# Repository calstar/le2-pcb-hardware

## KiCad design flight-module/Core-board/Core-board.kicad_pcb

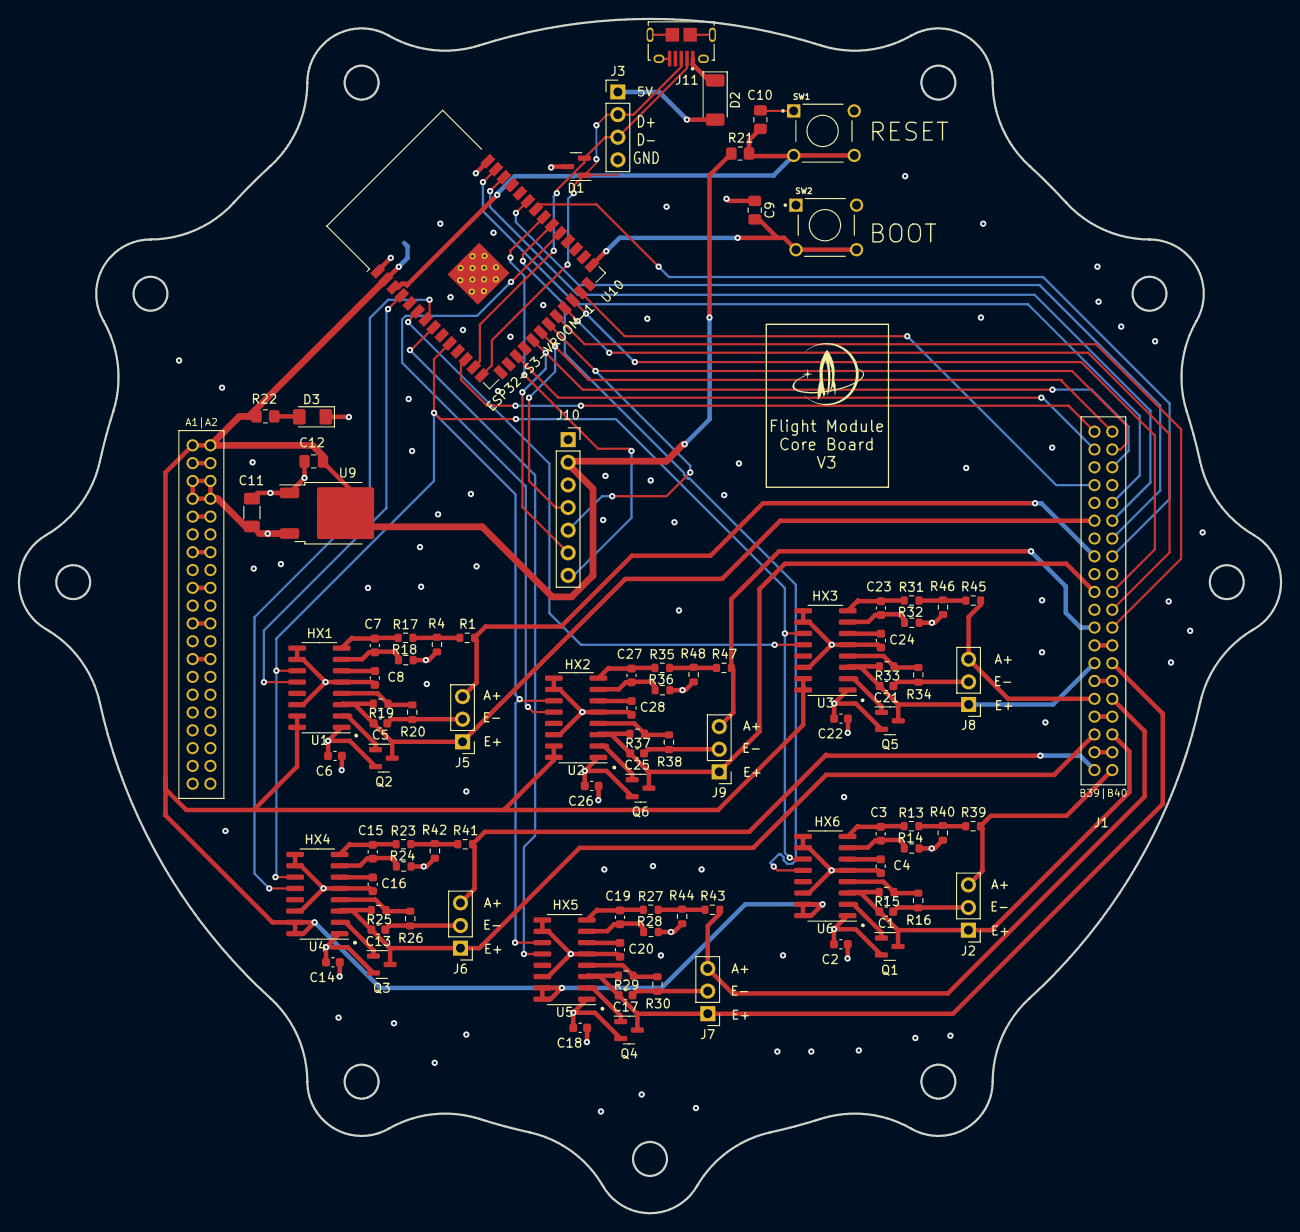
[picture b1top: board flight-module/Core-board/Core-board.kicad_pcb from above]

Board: 4 copper layers, 141.7 x 134.1 mm, 95 parts (0 on the bottom side), 78 nets.

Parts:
C1, C2, C5, C6, C13, C14, C17, C18, C21, C22, C25, C26: 10uF; C_0603_1608Metric
C3, C4, C7, C8, C15, C16, C19, C20, C23, C24, C27, C28: 0.1uF; C_0603_1608Metric
C9, C10: 1uF; C_0805_2012Metric_Pad1.18x1.45mm_HandSolder
C11: 10uF; C_1206_3216Metric_Pad1.33x1.80mm_HandSolder
C12: 22uF; C_0805_2012Metric_Pad1.18x1.45mm_HandSolder
D1: PESD12VL2BT; SOT-23
D2: D_Schottky; D_SOD-128
D3: GREEN; LED_1206_3216Metric_Pad1.42x1.75mm_HandSolder
J1: Stack_Shape
J2, J5, J6, J7, J8, J9: Conn_01x03_Pin; PinHeader_1x03_P2.54mm_Vertical
J3: Probe_points; PinHeader_1x04_P2.54mm_Vertical
J10: Conn_01x07_Pin; PinSocket_1x07_P2.54mm_Vertical
J11: 10118194-0011LF; AMPHENOL_10118194-0011LF
Q1, Q2, Q3, Q4, Q5, Q6: MMBT4403LT3G; SOT-23
R1, R39, R41, R43, R45, R47: 100kΩ; R_0603_1608Metric
R4, R40, R42, R44, R46, R48: 2kΩ; R_0603_1608Metric
R13, R14, R17, R18, R23, R24, R27, R28, R31, R32, R35, R36: 100Ω; R_0603_1608Metric
R15, R19, R25, R29, R33, R37: 20kΩ; R_0603_1608Metric
R16, R20, R26, R30, R34, R38: 8.2kΩ; R_0603_1608Metric
R21: 10k; R_0805_2012Metric_Pad1.20x1.40mm_HandSolder
R22: 300; R_0805_2012Metric_Pad1.20x1.40mm_HandSolder
SW1, SW2: 1825910-6; SW_1825910-6-4
U1, U2, U3, U4, U5, U6: HX711; SOP-16_3.9x9.9mm_P1.27mm
U9: AZ1084-3.3; TO-252-2
U10: ESP32-S3-WROOM-1-N16R2; ESP32-S3-WROOM-1

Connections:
+3.3V: C12.1, J1.A1 (Pin_1), J1.A2 (Pin_2), J10.2, R21.1, R22.2, U1.15 (RATE), U1.16 (DVDD), U2.15 (RATE), U2.16 (DVDD), U3.15 (RATE), U3.16 (DVDD), U4.15 (RATE), U4.16 (DVDD), U5.15 (RATE), U5.16 (DVDD), U6.15 (RATE), U6.16 (DVDD), U9.2 (VO), U10.2 (3V3)
+5V: C2.2, C6.2, C11.1, C14.2, C18.2, C22.2, C26.2, D2.2 (A), J1.A5 (Pin_5), J1.A6 (Pin_6), J1.A7 (Pin_7), J1.A8 (Pin_8), J3.1, Q1.2 (E), Q2.2 (E), Q3.2 (E), Q4.2 (E), Q5.2 (E), Q6.2 (E), U1.1 (VSUP), U2.1 (VSUP), U3.1 (VSUP), U4.1 (VSUP), U5.1 (VSUP), U6.1 (VSUP), U9.3 (VI)
/ESP32-S3-WROOM-1-Breakout/BOOT: C9.2, SW2.3, SW2.4, U10.27 (IO0)
/ESP32-S3-WROOM-1-Breakout/EN: C10.2, R21.2, SW1.3, SW1.4, U10.3 (EN)
/ESP32-S3-WROOM-1-Breakout/USB_D+: D1.1 (K), J3.2, J11.3 (D+), U10.14 (IO20)
/ESP32-S3-WROOM-1-Breakout/USB_D-: D1.2 (K), J3.3, J11.2 (D-), U10.13 (IO19)
/HX1_A+: J1.B15 (Pin_15), J5.3, R1.1
/HX1_DT: U1.12 (DOUT), U10.4 (IO4)
/HX1_E+: C5.2, J1.B11 (Pin_11), J5.1, Q2.3 (C), R19.2, U1.3 (AVDD)
/HX2_A+: J1.B23 (Pin_23), J9.3, R47.1
/HX2_DT: U2.12 (DOUT), U10.31 (IO38)
/HX2_E+: C25.2, J1.B19 (Pin_19), J9.1, Q6.3 (C), R37.2, U2.3 (AVDD)
/HX3_A+: J1.B31 (Pin_31), J8.3, R45.1
/HX3_DT: U3.12 (DOUT), U10.6 (IO6)
/HX3_E+: C21.2, J1.B27 (Pin_27), J8.1, Q5.3 (C), R33.2, U3.3 (AVDD)
/HX4_A+: J1.B39 (Pin_39), J6.3, R41.1
/HX4_DT: U4.12 (DOUT), U10.7 (IO7)
/HX4_E+: C13.2, J1.B35 (Pin_35), J6.1, Q3.3 (C), R25.2, U4.3 (AVDD)
/HX5_A+: J1.B32 (Pin_32), J7.3, R43.1
/HX5_DT: U5.12 (DOUT), U10.8 (IO15)
/HX5_E+: C17.2, J1.B28 (Pin_28), J7.1, Q4.3 (C), R29.2, U5.3 (AVDD)
/HX6_A+: J1.B40 (Pin_40), J2.3, R39.1
/HX6_DT: U6.12 (DOUT), U10.32 (IO39)
/HX6_E+: C1.2, J1.B36 (Pin_36), J2.1, Q1.3 (C), R15.2, U6.3 (AVDD)
/HX_CLK: U1.11 (PD_SCK), U2.11 (PD_SCK), U3.11 (PD_SCK), U4.11 (PD_SCK), U5.11 (PD_SCK), U6.11 (PD_SCK), U10.10 (IO17)
/I2C_SCL: J1.B3 (Pin_3), U10.17 (IO9)
/I2C_SDA: J1.B1 (Pin_1), U10.12 (IO8)
/PYRO1EN: J1.B7 (Pin_7), U10.25 (IO48)
/PYRO2EN: J1.B20 (Pin_20), U10.24 (IO47)
/PYRO3EN: J1.B22 (Pin_22), U10.23 (IO21)
/PYRO4EN: J1.B24 (Pin_24), U10.22 (IO14)
/SD_CS: J10.7, U10.33 (IO40)
/SPI_CLK: J1.B2 (Pin_2), J10.4, U10.20 (IO12)
/SPI_MISO: J1.B4 (Pin_4), J10.5, U10.21 (IO13)
/SPI_MOSI: J1.B6 (Pin_6), J10.6, U10.19 (IO11)
/TC1_CS: J1.B10 (Pin_10), U10.39 (IO1)
/TC2_CS: J1.B12 (Pin_12), U10.38 (IO2)
/TC3_CS: J1.B14 (Pin_14), U10.35 (IO42)
/TC4_CS: J1.B16 (Pin_16), U10.34 (IO41)
GND: C1.1, C2.1, C4.1, C5.1, C6.1, C8.1, C9.1, C10.1, C11.2, C12.2, C13.1, C14.1, C16.1, C17.1, C18.1, C20.1, C21.1, C22.1, C24.1, C25.1, C26.1, C28.1, D1.3 (A), D3.1 (K), J1.A3 (Pin_3), J1.A4 (Pin_4), J1.A9 (Pin_9), J1.A10 (Pin_10), J1.A13 (Pin_13), J1.A14 (Pin_14), J1.A17 (Pin_17), J1.A18 (Pin_18), J1.A21 (Pin_21), J1.A22 (Pin_22), J1.A25 (Pin_25), J1.A26 (Pin_26), J1.B5 (Pin_5), J1.B8 (Pin_8), J1.B9 (Pin_9), J1.B13 (Pin_13), J1.B17 (Pin_17), J1.B18 (Pin_18), J1.B21 (Pin_21), J1.B25 (Pin_25), J1.B26 (Pin_26), J1.B29 (Pin_29), J1.B30 (Pin_30), J1.B33 (Pin_33), J1.B34 (Pin_34), J1.B37 (Pin_37), J1.B38 (Pin_38), J2.2, J3.4, J5.2, J6.2, J7.2, J8.2, J9.2, J10.3, J11.5 (GND), J11.S1 (SHIELD), J11.S2 (SHIELD__1), J11.S3 (SHIELD__2), J11.S4 (SHIELD__3), J11.S5 (SHIELD__4), J11.S6 (SHIELD__5), R4.1, R14.2, R16.1, R18.2, R20.1, R24.2, R26.1, R28.2, R30.1, R32.2, R34.1, R36.2, R38.1, R40.1, R42.1, R44.1, R46.1, R48.1, SW1.1, SW1.2, SW2.1, SW2.2, U1.5 (AGND), U1.9 (INB-), U1.10 (INB+), U1.14 (XI), U2.5 (AGND), U2.9 (INB-), U2.10 (INB+), U2.14 (XI), U3.5 (AGND), U3.9 (INB-), U3.10 (INB+), U3.14 (XI), U4.5 (AGND), U4.9 (INB-), U4.10 (INB+), U4.14 (XI), U5.5 (AGND), U5.9 (INB-), U5.10 (INB+), U5.14 (XI), U6.5 (AGND), U6.9 (INB-), U6.10 (INB+), U6.14 (XI), U9.1 (GND), U10.1 (GND), U10.40 (GND__1), U10.41 (GND__2)
unnamed: D2.1 (K), J11.1 (VBUS)
unnamed: D3.2 (A), R22.1
unnamed: Q1.1 (B), U6.2 (BASE)
unnamed: Q2.1 (B), U1.2 (BASE)
unnamed: Q3.1 (B), U4.2 (BASE)
unnamed: Q4.1 (B), U5.2 (BASE)
unnamed: Q5.1 (B), U3.2 (BASE)
unnamed: Q6.1 (B), U2.2 (BASE)
unnamed: R1.2, R4.2, R17.2
unnamed: R13.2, R39.2, R40.2
unnamed: R23.2, R41.2, R42.2
unnamed: R27.2, R43.2, R44.2
unnamed: R31.2, R45.2, R46.2
unnamed: R35.2, R47.2, R48.2
unnamed: C7.2, R17.1, U1.8 (INA+)
unnamed: C7.1, R18.1, U1.7 (INA-)
unnamed: C8.2, U1.6 (VBG)
unnamed: R19.1, R20.2, U1.4 (VFB)
unnamed: C27.2, R35.1, U2.8 (INA+)
unnamed: C27.1, R36.1, U2.7 (INA-)
unnamed: C28.2, U2.6 (VBG)
unnamed: R37.1, R38.2, U2.4 (VFB)
unnamed: C23.2, R31.1, U3.8 (INA+)
unnamed: C23.1, R32.1, U3.7 (INA-)
unnamed: C24.2, U3.6 (VBG)
unnamed: R33.1, R34.2, U3.4 (VFB)
unnamed: C15.2, R23.1, U4.8 (INA+)
unnamed: C15.1, R24.1, U4.7 (INA-)
unnamed: C16.2, U4.6 (VBG)
unnamed: R25.1, R26.2, U4.4 (VFB)
unnamed: C19.2, R27.1, U5.8 (INA+)
unnamed: C19.1, R28.1, U5.7 (INA-)
unnamed: C20.2, U5.6 (VBG)
unnamed: R29.1, R30.2, U5.4 (VFB)
unnamed: C3.2, R13.1, U6.8 (INA+)
unnamed: C3.1, R14.1, U6.7 (INA-)
unnamed: C4.2, U6.6 (VBG)
unnamed: R15.1, R16.2, U6.4 (VFB)

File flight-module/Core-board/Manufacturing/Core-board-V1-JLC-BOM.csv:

Comment,Designator,Footprint,LCSC
10uF,"C1,C2,C5,C6,C13,C14,C17,C18,C21,C22,C25,C26",Capacitor_SMD:C_0603_1608Metric,
10uF,C11,Capacitor_SMD:C_1206_3216Metric_Pad1.33x1.80mm_HandSolder,
22uF,C12,Capacitor_SMD:C_0805_2012Metric_Pad1.18x1.45mm_HandSolder,
0.1uF,"C3,C4,C7,C8,C15,C16,C19,C20,C23,C24,C27,C28",Capacitor_SMD:C_0603_1608Metric,
1uF,"C9,C10",Capacitor_SMD:C_0805_2012Metric_Pad1.18x1.45mm_HandSolder,
PESD12VL2BT,D1,Package_TO_SOT_SMD:SOT-23,
"PMEG3050EP,115",D2,Diode_SMD:D_SOD-128,
EL0603/GHC-C01/DT,D3,LED_SMD:LED_1206_3216Metric_Pad1.42x1.75mm_HandSolder,
MMBT4403LT3G,"Q1,Q2,Q3,Q4,Q5,Q6",Package_TO_SOT_SMD:SOT-23,
100Ω,"R13,R14,R17,R18,R23,R24,R27,R28,R31,R32,R35,R36",Resistor_SMD:R_0603_1608Metric,
20kΩ,"R15,R19,R25,R29,R33,R37",Resistor_SMD:R_0603_1608Metric,
8.2kΩ,"R16,R20,R26,R30,R34,R38",Resistor_SMD:R_0603_1608Metric,
10k,R21,Resistor_SMD:R_0805_2012Metric_Pad1.20x1.40mm_HandSolder,
300,R22,Resistor_SMD:R_0805_2012Metric_Pad1.20x1.40mm_HandSolder,
100kΩ,"R1,R39,R41,R43,R45,R47",Resistor_SMD:R_0603_1608Metric,
2kΩ,"R4,R40,R42,R44,R46,R48",Resistor_SMD:R_0603_1608Metric,
1825910-6,"SW1,SW2",Button_Switch_SMD:SW_SPST_TL3305A,
ESP32-S3-WROOM-1-N16R2,U10,RF_Module:ESP32-S3-WROOM-1,
XTSD04GLGEAG,U7,XTSD04GLGEAG:SON127P600X800X95-8N,
74HC4050D,U8,74HC4050D:SO16,
AZ1084-3.3,U9,Package_TO_SOT_SMD:TO-252-2,

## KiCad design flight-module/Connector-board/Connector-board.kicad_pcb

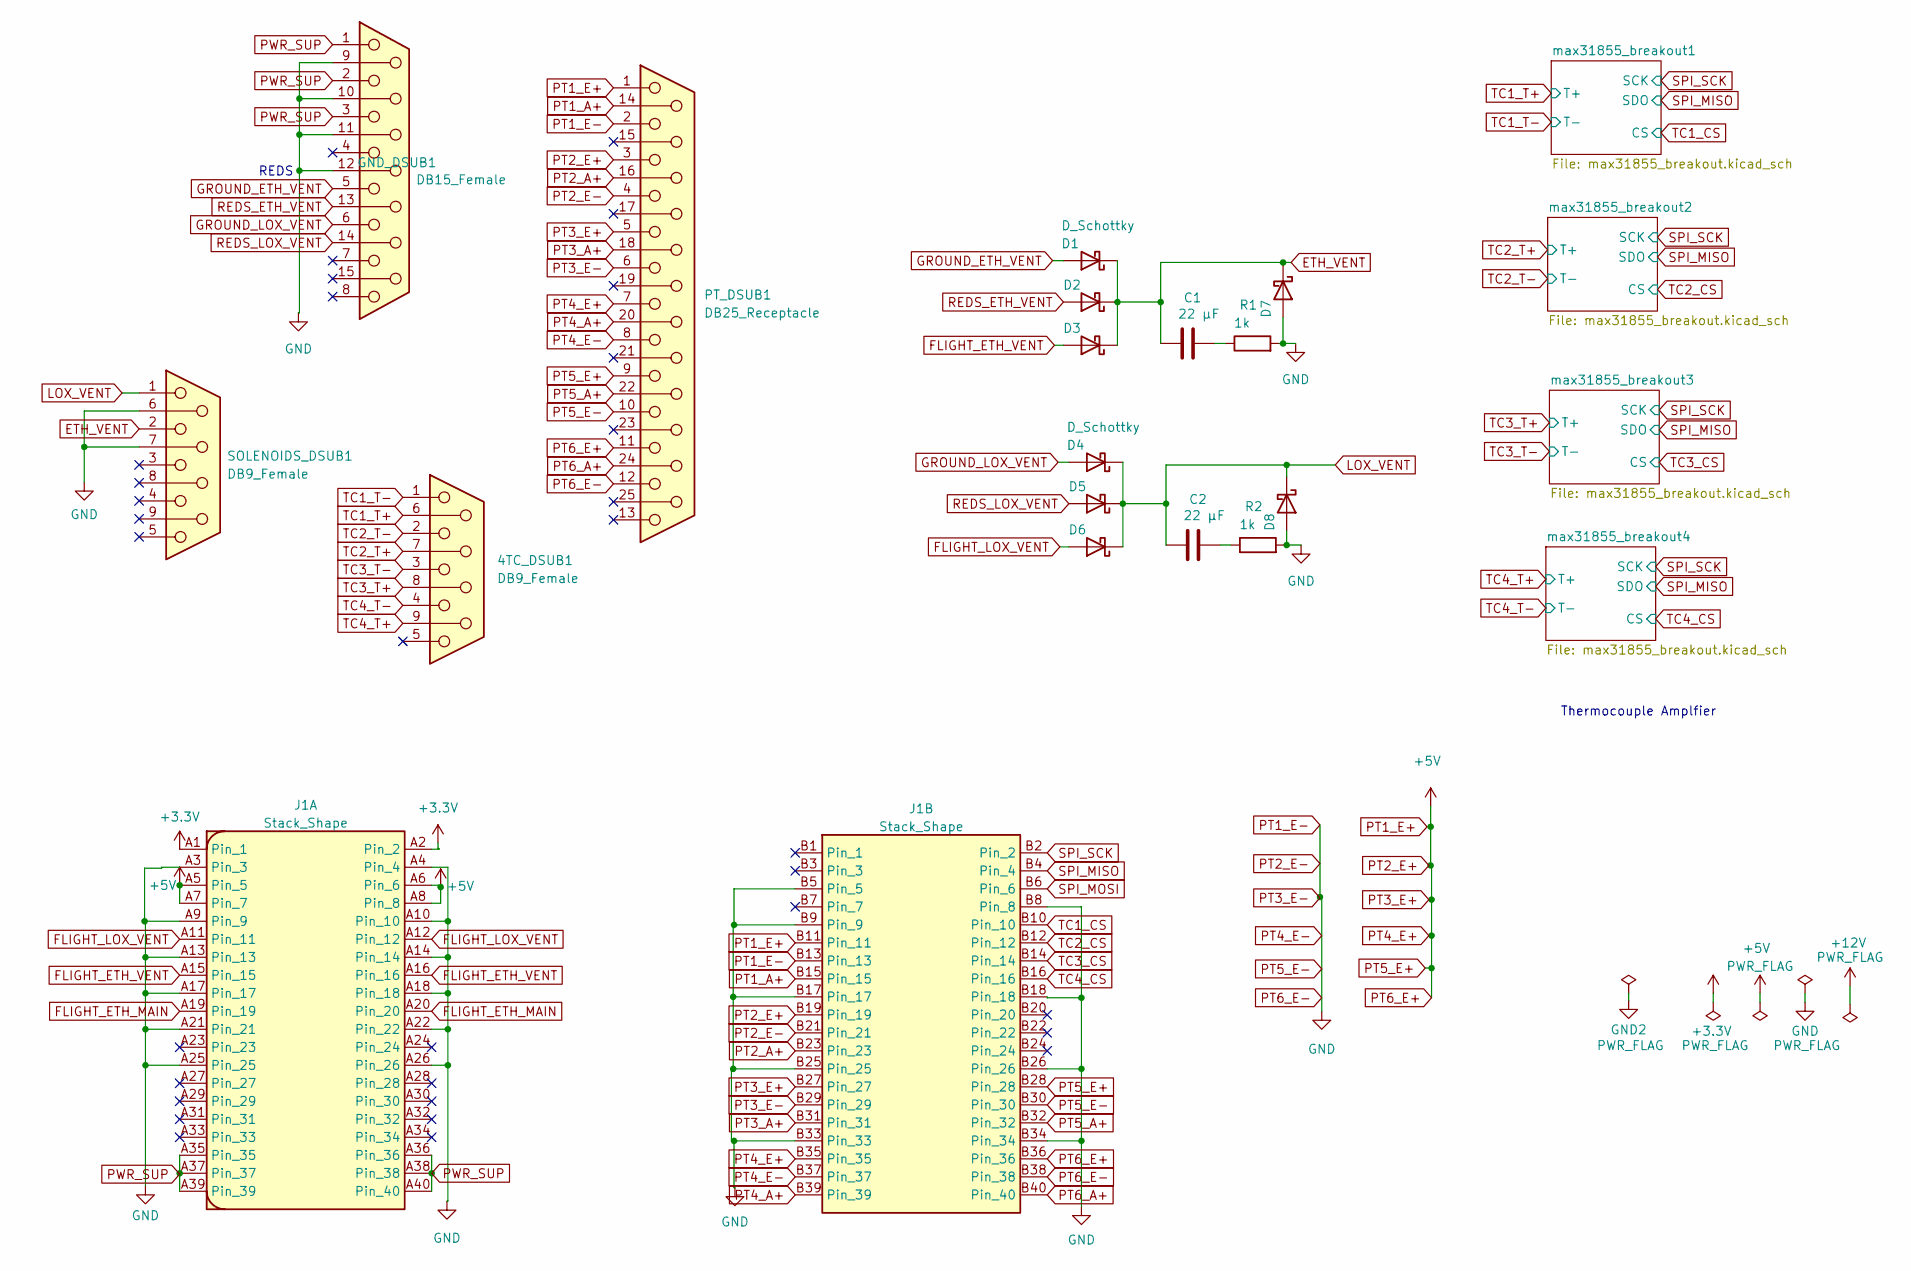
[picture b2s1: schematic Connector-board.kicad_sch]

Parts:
4TC_DSUB1: DB9_Female; DSUB-9_Female_Vertical_P2.77x2.84mm_MountingHoles
C1, C2: 22 µF; D_0603_1608Metric
D1, D2, D3, D4, D5, D6, D7, D8: D_Schottky; D_SOD-128
GND_DSUB1: DB15_Female; DSUB-15_Female_Vertical_P2.77x2.84mm_MountingHoles
J1: Stack_Shape
PT_DSUB1: DB25_Receptacle; DSUB-25_Female_Vertical_P2.77x2.84mm_MountingHoles
R1, R2: 1k; D_0603_1608Metric
SOLENOIDS_DSUB1: DB9_Female; DSUB-9_Female_Vertical_P2.77x2.84mm_MountingHoles

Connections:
+3.3V: J1.A1 (Pin_1), J1.A2 (Pin_2); also elsewhere on the board
ETH_VENT: C1.1, D1.1 (K), D2.1 (K), D3.1 (K), D7.1 (K), SOLENOIDS_DSUB1.2
FLIGHT_ETH_MAIN: J1.A19 (Pin_19), J1.A20 (Pin_20)
FLIGHT_ETH_VENT: D3.2 (A), J1.A15 (Pin_15), J1.A16 (Pin_16)
FLIGHT_LOX_VENT: D6.2 (A), J1.A11 (Pin_11), J1.A12 (Pin_12)
GROUND_ETH_VENT: D1.2 (A), GND_DSUB1.5
GROUND_LOX_VENT: D4.2 (A), GND_DSUB1.6
LOX_VENT: C2.1, D4.1 (K), D5.1 (K), D6.1 (K), D8.1 (K), SOLENOIDS_DSUB1.1
unnamed: C1.2, R1.1
unnamed: C2.2, R2.1
PT1_A+: J1.B15 (Pin_15), PT_DSUB1.14
PT1_E+: J1.A5 (Pin_5), J1.A6 (Pin_6), J1.A7 (Pin_7), J1.A8 (Pin_8), J1.B11 (Pin_11), J1.B19 (Pin_19), J1.B27 (Pin_27), J1.B28 (Pin_28), J1.B35 (Pin_35), J1.B36 (Pin_36), PT_DSUB1.1, PT_DSUB1.3, PT_DSUB1.5, PT_DSUB1.7, PT_DSUB1.9, PT_DSUB1.11
PT1_E-: D7.2 (A), D8.2 (A), GND_DSUB1.9, GND_DSUB1.10, GND_DSUB1.11 (P111), GND_DSUB1.12, J1.A3 (Pin_3), J1.A4 (Pin_4), J1.A9 (Pin_9), J1.A10 (Pin_10), J1.A13 (Pin_13), J1.A14 (Pin_14), J1.A17 (Pin_17), J1.A18 (Pin_18), J1.A21 (Pin_21), J1.A22 (Pin_22), J1.A25 (Pin_25), J1.A26 (Pin_26), J1.B5 (Pin_5), J1.B8 (Pin_8), J1.B9 (Pin_9), J1.B13 (Pin_13), J1.B17 (Pin_17), J1.B18 (Pin_18), J1.B21 (Pin_21), J1.B25 (Pin_25), J1.B26 (Pin_26), J1.B29 (Pin_29), J1.B30 (Pin_30), J1.B33 (Pin_33), J1.B34 (Pin_34), J1.B37 (Pin_37), J1.B38 (Pin_38), PT_DSUB1.2, PT_DSUB1.4, PT_DSUB1.6, PT_DSUB1.8, PT_DSUB1.10, PT_DSUB1.12, R1.2, R2.2, SOLENOIDS_DSUB1.6, SOLENOIDS_DSUB1.7; also elsewhere on the board
PT2_A+: J1.B23 (Pin_23), PT_DSUB1.16
PT3_A+: J1.B31 (Pin_31), PT_DSUB1.18
PT4_A+: J1.B39 (Pin_39), PT_DSUB1.20
PT5_A+: J1.B32 (Pin_32), PT_DSUB1.22
PT6_A+: J1.B40 (Pin_40), PT_DSUB1.24
PWR_SUP: GND_DSUB1.1, GND_DSUB1.2, GND_DSUB1.3, J1.A35 (Pin_35), J1.A36 (Pin_36), J1.A37 (Pin_37), J1.A38 (Pin_38), J1.A39 (Pin_39), J1.A40 (Pin_40)
REDS_ETH_VENT: D2.2 (A), GND_DSUB1.13
REDS_LOX_VENT: D5.2 (A), GND_DSUB1.14
SPI_MISO: J1.B4 (Pin_4); also elsewhere on the board
SPI_MOSI: J1.B6 (Pin_6)
SPI_SCK: J1.B2 (Pin_2); also elsewhere on the board
TC1_CS: J1.B10 (Pin_10); also elsewhere on the board
TC1_T+: 4TC_DSUB1.6; also elsewhere on the board
TC1_T-: 4TC_DSUB1.1; also elsewhere on the board
TC2_CS: J1.B12 (Pin_12); also elsewhere on the board
TC2_T+: 4TC_DSUB1.7; also elsewhere on the board
TC2_T-: 4TC_DSUB1.2; also elsewhere on the board
TC3_CS: J1.B14 (Pin_14); also elsewhere on the board
TC3_T+: 4TC_DSUB1.8; also elsewhere on the board
TC3_T-: 4TC_DSUB1.3; also elsewhere on the board
TC4_CS: J1.B16 (Pin_16); also elsewhere on the board
TC4_T+: 4TC_DSUB1.9; also elsewhere on the board
TC4_T-: 4TC_DSUB1.4; also elsewhere on the board

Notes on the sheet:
Thermocouple Amplfier
REDS

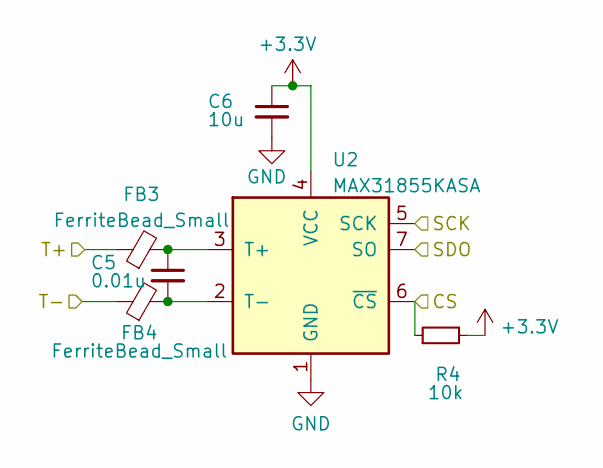
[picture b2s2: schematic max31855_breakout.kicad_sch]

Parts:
C5: 0.01u; C_0603_1608Metric
C6: 10u; C_0603_1608Metric
FB3, FB4: FerriteBead_Small; C_0603_1608Metric
R4: 10k; R_0603_1608Metric
U2: MAX31855KASA; SOIC-8_3.9x4.9mm_P1.27mm

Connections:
+3.3V: C6.1, R4.2, U2.4 (VCC); also elsewhere on the board
unnamed: C5.1, FB3.2, U2.3 (T+)
unnamed: C5.2, FB4.2, U2.2 (T-)
PT1_E-: C6.2, U2.1 (GND); also elsewhere on the board
SPI_MISO: U2.7 (SO); also elsewhere on the board
SPI_SCK: U2.5 (SCK); also elsewhere on the board
TC4_CS: R4.1, U2.6 (~CS); also elsewhere on the board
TC4_T+: FB3.1; also elsewhere on the board
TC4_T-: FB4.1; also elsewhere on the board

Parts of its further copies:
C3, C7, C9: 0.01u; C_0603_1608Metric
C4, C8, C10: 10u; C_0603_1608Metric
FB1, FB2, FB5, FB6, FB7, FB8: FerriteBead_Small; C_0603_1608Metric
R3, R5, R6: 10k; R_0603_1608Metric
U1, U3, U4: MAX31855KASA; SOIC-8_3.9x4.9mm_P1.27mm

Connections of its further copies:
+3.3V: C4.1, C8.1, C10.1, R3.2, R5.2, R6.2, U1.4 (VCC), U3.4 (VCC), U4.4 (VCC); also elsewhere on the board
unnamed: C3.1, FB1.2, U1.3 (T+)
unnamed: C3.2, FB2.2, U1.2 (T-)
unnamed: C7.1, FB5.2, U3.3 (T+)
unnamed: C7.2, FB6.2, U3.2 (T-)
unnamed: C9.1, FB7.2, U4.3 (T+)
unnamed: C9.2, FB8.2, U4.2 (T-)
PT1_E-: C4.2, C8.2, C10.2, U1.1 (GND), U3.1 (GND), U4.1 (GND); also elsewhere on the board
SPI_MISO: U1.7 (SO), U3.7 (SO), U4.7 (SO); also elsewhere on the board
SPI_SCK: U1.5 (SCK), U3.5 (SCK), U4.5 (SCK); also elsewhere on the board
TC1_CS: R3.1, U1.6 (~CS); also elsewhere on the board
TC1_T+: FB1.1; also elsewhere on the board
TC1_T-: FB2.1; also elsewhere on the board
TC2_CS: R5.1, U3.6 (~CS); also elsewhere on the board
TC2_T+: FB5.1; also elsewhere on the board
TC2_T-: FB6.1; also elsewhere on the board
TC3_CS: R6.1, U4.6 (~CS); also elsewhere on the board
TC3_T+: FB7.1; also elsewhere on the board
TC3_T-: FB8.1; also elsewhere on the board

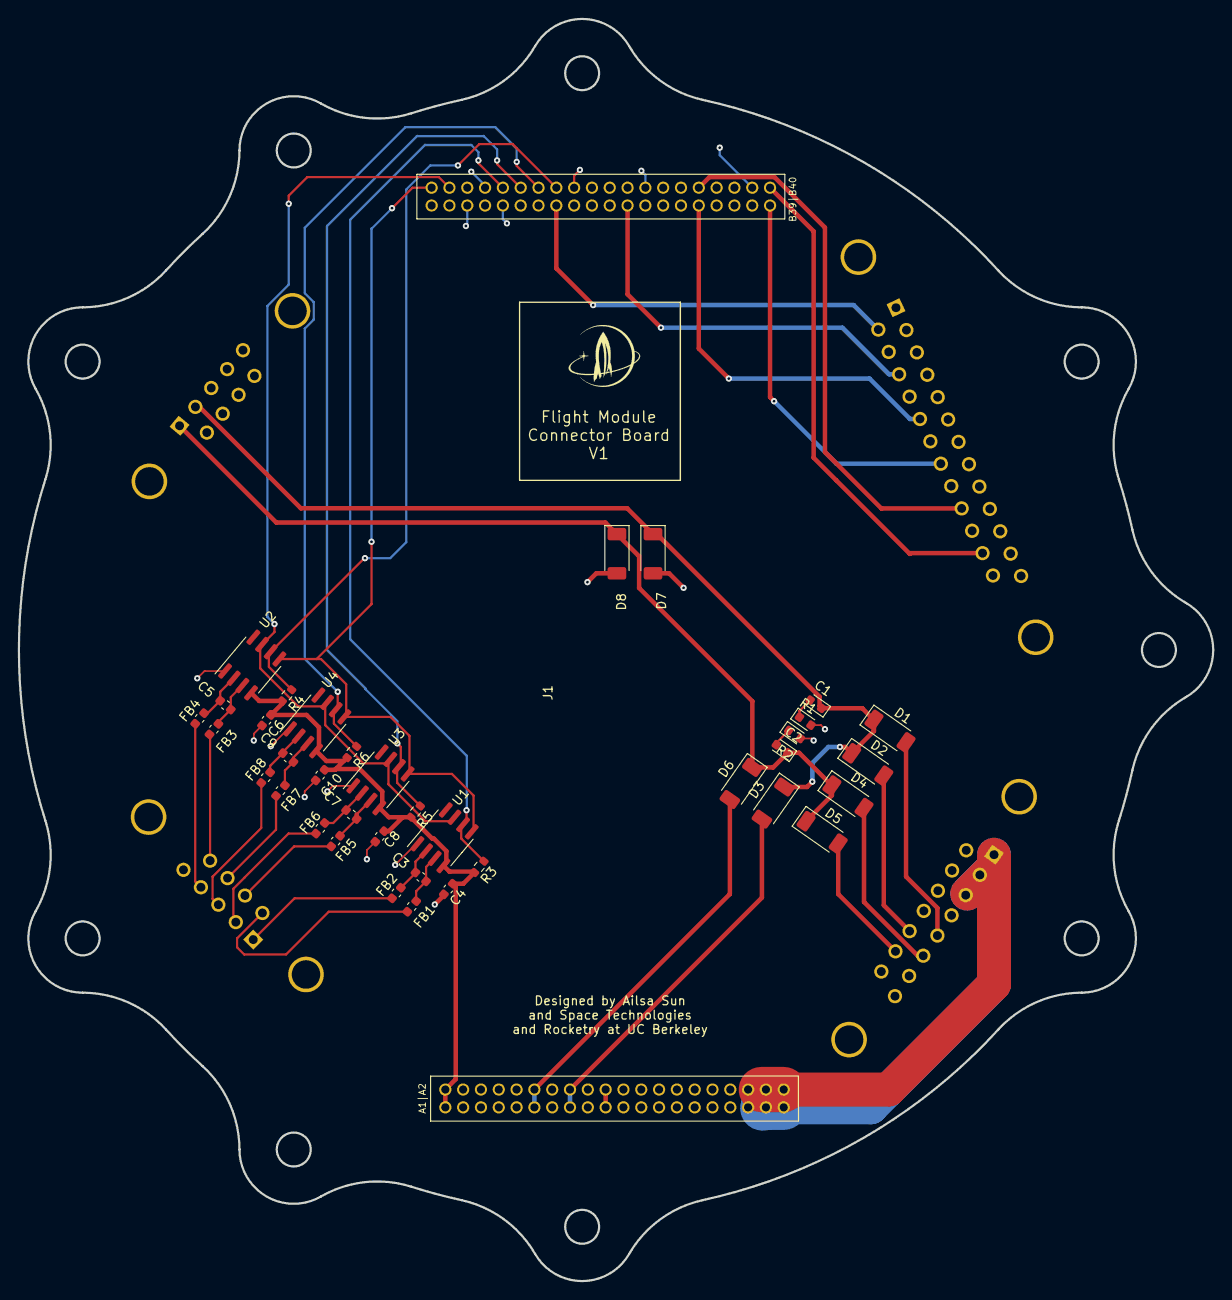
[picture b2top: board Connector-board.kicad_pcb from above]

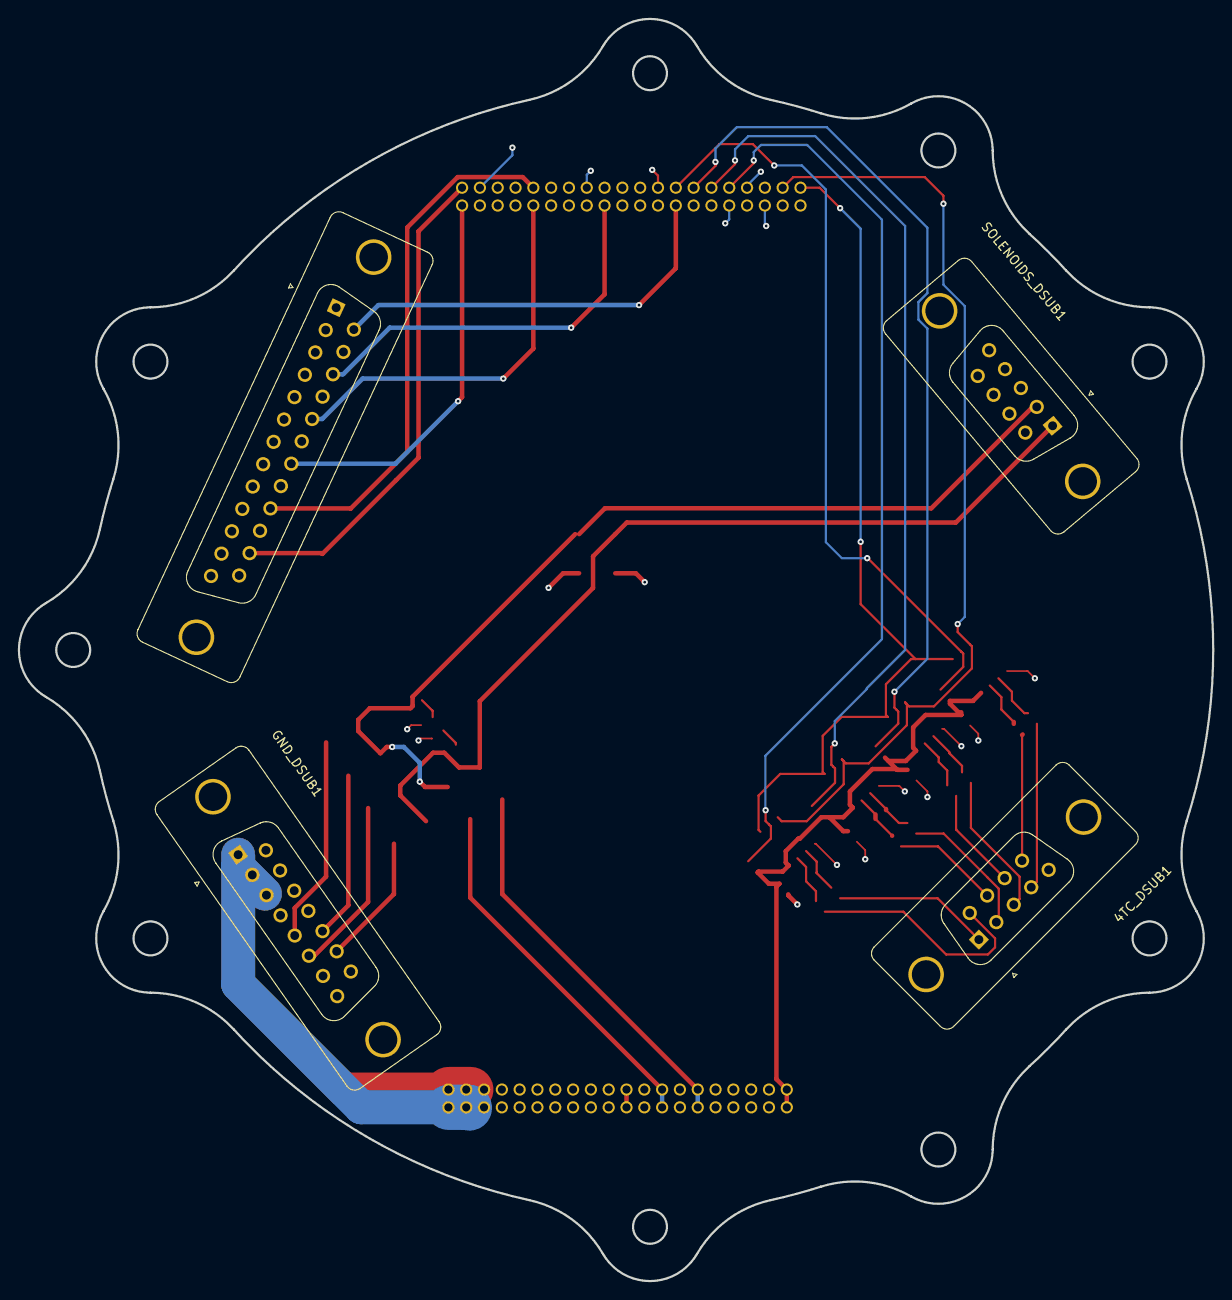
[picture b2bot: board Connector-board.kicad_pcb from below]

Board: 4 copper layers, 134.1 x 141.7 mm, 41 parts (4 on the bottom side), 43 nets.

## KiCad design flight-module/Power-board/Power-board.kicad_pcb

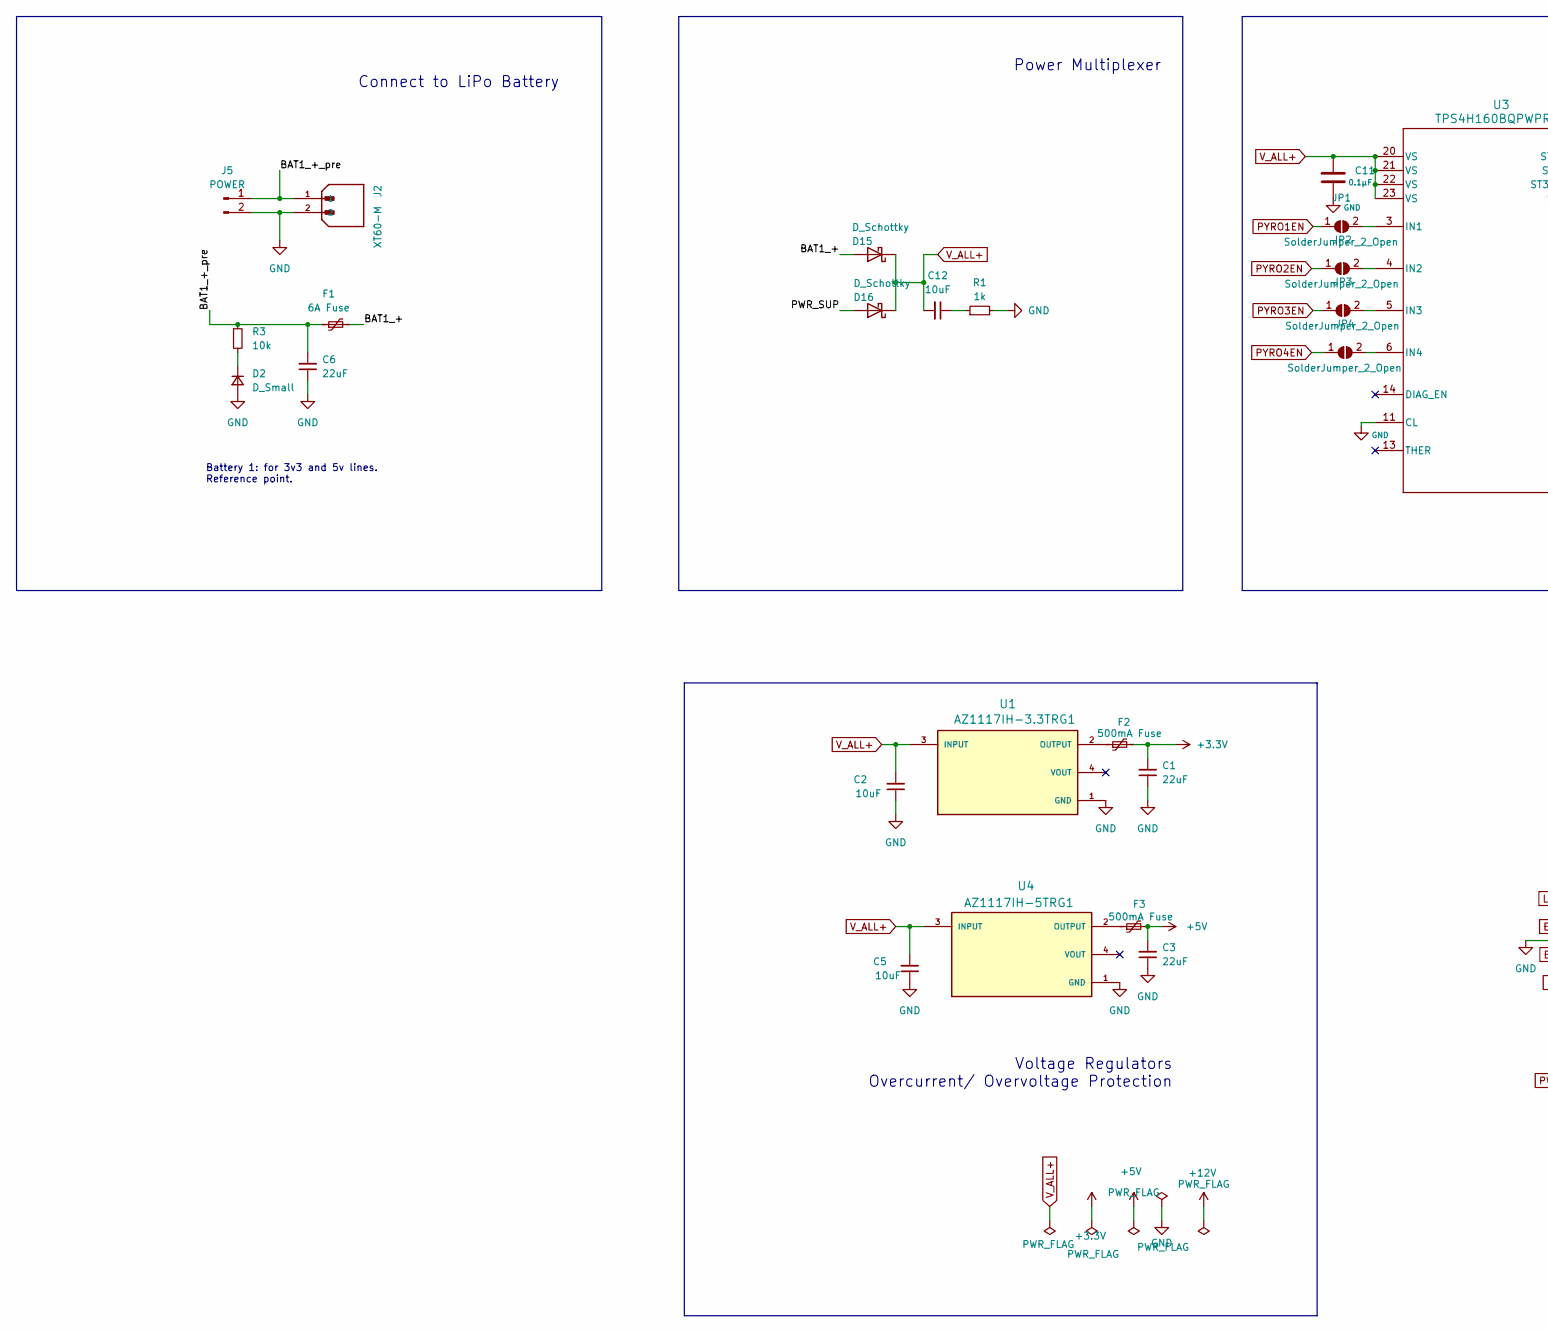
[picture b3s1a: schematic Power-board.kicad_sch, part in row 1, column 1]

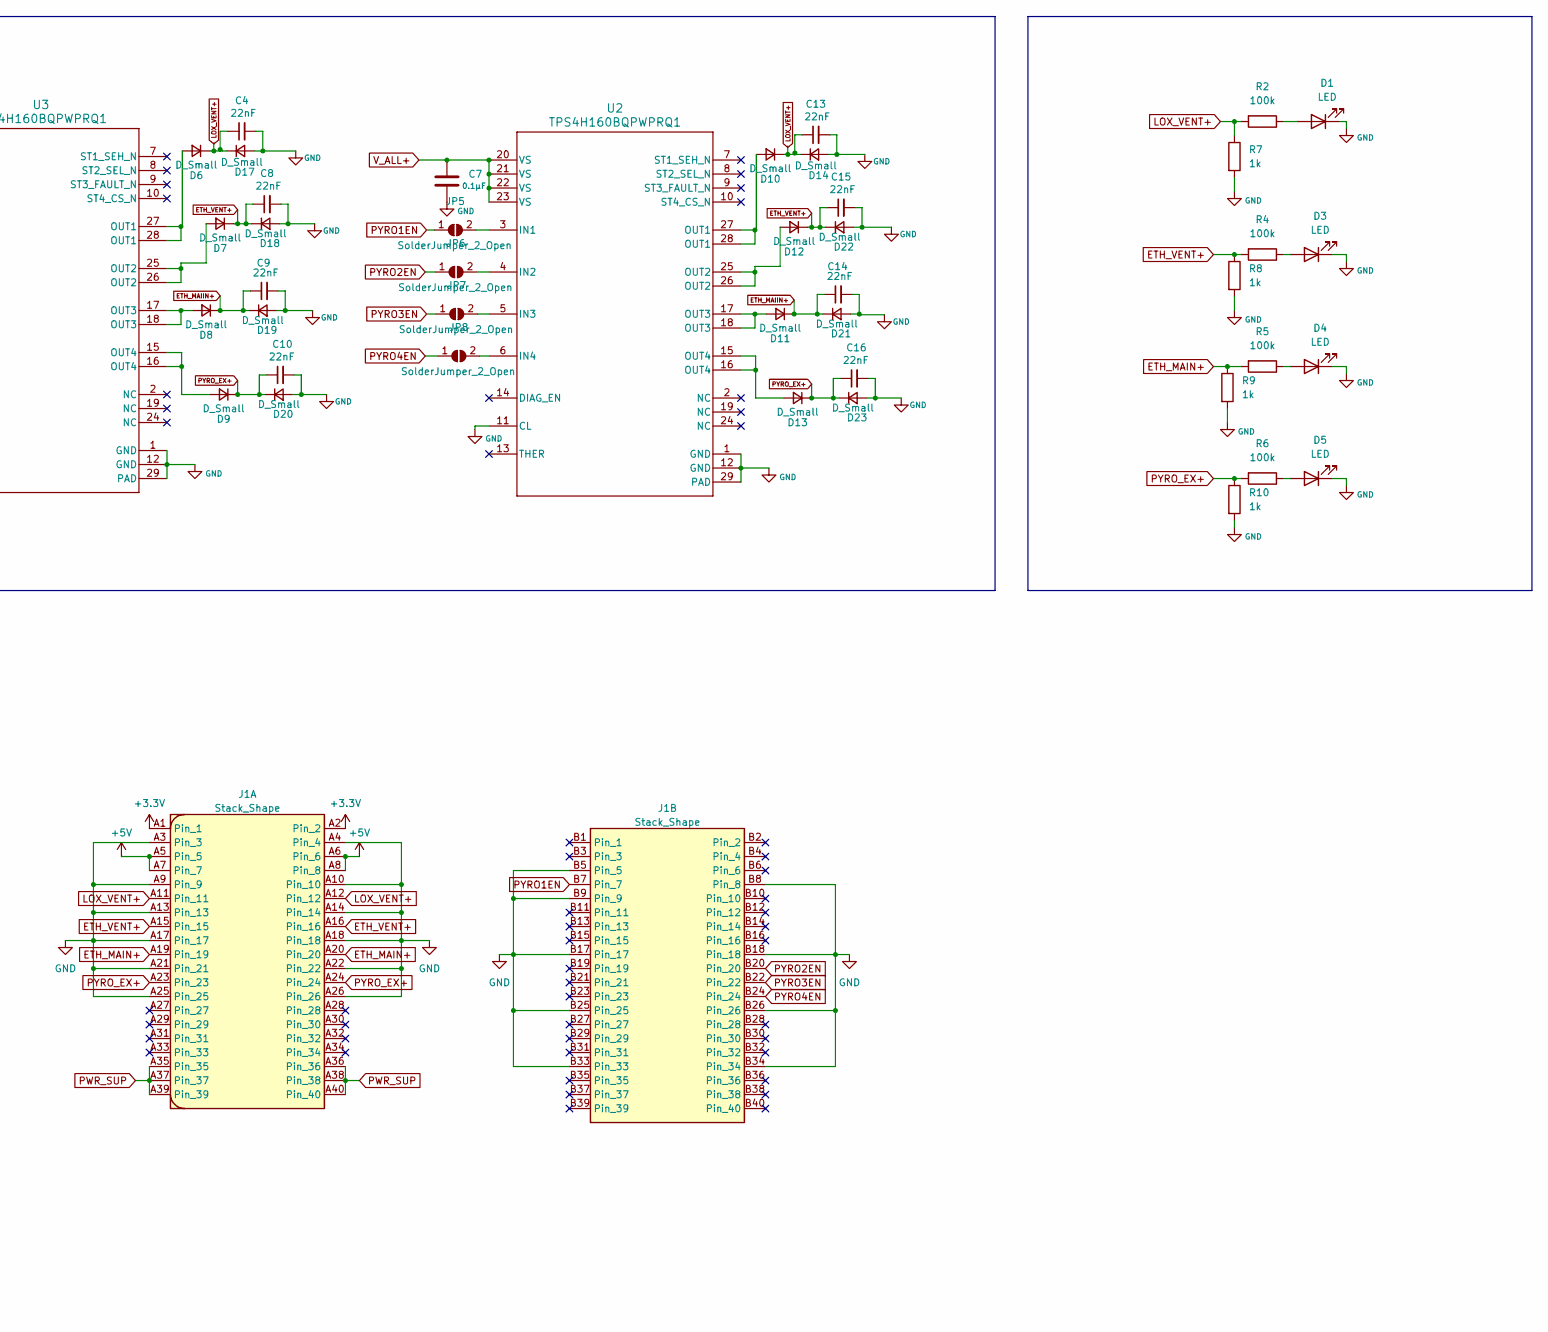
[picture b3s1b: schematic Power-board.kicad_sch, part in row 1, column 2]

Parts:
C1, C3, C6: 22uF; C_0603_1608Metric
C2, C5, C12: 10uF; C_0603_1608Metric
C4, C8, C9, C10, C13, C14, C15, C16: 22nF; C_0603_1608Metric
C7, C11: 0.1µF; C_0603_1608Metric
D1, D3, D4, D5: LED; LED_0603_1608Metric_Pad1.05x0.95mm_HandSolder
D2, D6, D7, D8, D9, D10, D11, D12, D13, D14, D17, D18, D19, D20, D21, D22, D23: D_Small; D_0603_1608Metric
D15, D16: D_Schottky; SMADO-214AC_LEAD-FRAME_MCC
F1: 6A Fuse; Fuse_2920_7451Metric
F2, F3: 500mA Fuse; Fuse_0603_1608Metric
J1: Stack_Shape
J2: XT60-M; AMASS_XT60PW-F_1x02_P7.20mm_Horizontal; PARTREV V1.2
J5: POWER; Banana_Jack_2Pin
JP1, JP2, JP3, JP4, JP5, JP6, JP7, JP8: SolderJumper_2_Open; SolderJumper-2_P1.3mm_Bridged_RoundedPad1.0x1.5mm
R1, R7, R8, R9, R10: 1k; R_0603_1608Metric
R2, R4, R5, R6: 100k; R_0603_1608Metric
R3: 10k; R_0603_1608Metric
U1: AZ1117IH-3.3TRG1; SOT223_AZ1117I_6P5X3P5_DIO; PARTREV 2-2
U2, U3: TPS4H160BQPWPRQ1; PWP0028C_N
U4: AZ1117IH-5TRG1; SOT223_AZ1117I_6P5X3P5_DIO; PARTREV 2-2

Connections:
+3.3V: C1.2, F2.2, J1.A1 (Pin_1), J1.A2 (Pin_2)
+5V: C3.2, F3.2, J1.A5 (Pin_5), J1.A6 (Pin_6), J1.A7 (Pin_7), J1.A8 (Pin_8)
/BAT1_+: D15.2 (A), F1.2
/BAT1_+_pre: C6.2, F1.1, J2.1, J5.1, R3.1
ETH_MAIIN+: C9.1, C14.1, D8.1 (K), D11.1 (K), D19.1 (K), D21.1 (K)
ETH_MAIN+: J1.A19 (Pin_19), J1.A20 (Pin_20), R5.2, R9.1
ETH_VENT+: C8.1, C15.1, D7.1 (K), D12.1 (K), D18.1 (K), D22.1 (K), J1.A15 (Pin_15), J1.A16 (Pin_16), R4.2, R8.1
GND: C1.1, C2.1, C3.1, C4.2, C5.1, C6.1, C7.2, C8.2, C9.2, C10.2, C11.2, C13.2, C14.2, C15.2, C16.2, D1.1 (K), D2.2 (A), D3.1 (K), D4.1 (K), D5.1 (K), D14.2 (A), D17.2 (A), D18.2 (A), D19.2 (A), D20.2 (A), D21.2 (A), D22.2 (A), D23.2 (A), J1.A3 (Pin_3), J1.A4 (Pin_4), J1.A9 (Pin_9), J1.A10 (Pin_10), J1.A13 (Pin_13), J1.A14 (Pin_14), J1.A17 (Pin_17), J1.A18 (Pin_18), J1.A21 (Pin_21), J1.A22 (Pin_22), J1.A25 (Pin_25), J1.A26 (Pin_26), J1.B5 (Pin_5), J1.B8 (Pin_8), J1.B9 (Pin_9), J1.B17 (Pin_17), J1.B18 (Pin_18), J1.B25 (Pin_25), J1.B26 (Pin_26), J1.B33 (Pin_33), J1.B34 (Pin_34), J2.2, J5.2, R1.2, R7.2, R8.2, R9.2, R10.2, U1.1 (GND), U2.1 (GND), U2.11 (CL), U2.12 (GND), U2.29 (PAD), U3.1 (GND), U3.11 (CL), U3.12 (GND), U3.29 (PAD), U4.1 (GND)
LOX_VENT+: C4.1, C13.1, D6.1 (K), D10.1 (K), D14.1 (K), D17.1 (K), J1.A11 (Pin_11), J1.A12 (Pin_12), R2.2, R7.1
unnamed: C12.1, R1.1
unnamed: D1.2 (A), R2.1
unnamed: D2.1 (K), R3.2
unnamed: D3.2 (A), R4.1
unnamed: D4.2 (A), R5.1
unnamed: D5.2 (A), R6.1
unnamed: D6.2 (A), U3.27 (OUT1), U3.28 (OUT1)
unnamed: D7.2 (A), U3.25 (OUT2), U3.26 (OUT2)
unnamed: D8.2 (A), U3.17 (OUT3), U3.18 (OUT3)
unnamed: D9.2 (A), U3.15 (OUT4), U3.16 (OUT4)
unnamed: D10.2 (A), U2.27 (OUT1), U2.28 (OUT1)
unnamed: D11.2 (A), U2.17 (OUT3), U2.18 (OUT3)
unnamed: D12.2 (A), U2.25 (OUT2), U2.26 (OUT2)
unnamed: D13.2 (A), U2.15 (OUT4), U2.16 (OUT4)
unnamed: JP1.2 (B), U3.3 (IN1)
unnamed: JP2.2 (B), U3.4 (IN2)
unnamed: JP3.2 (B), U3.5 (IN3)
unnamed: JP4.2 (B), U3.6 (IN4)
unnamed: JP5.2 (B), U2.3 (IN1)
unnamed: JP6.2 (B), U2.4 (IN2)
unnamed: JP7.2 (B), U2.5 (IN3)
unnamed: JP8.2 (B), U2.6 (IN4)
unnamed: F2.1, U1.2 (OUTPUT)
unnamed: F3.1, U4.2 (OUTPUT)
PWR_SUP: D16.2 (A), J1.A35 (Pin_35), J1.A36 (Pin_36), J1.A37 (Pin_37), J1.A38 (Pin_38), J1.A39 (Pin_39), J1.A40 (Pin_40)
PYRO1EN: J1.B7 (Pin_7), JP1.1 (A), JP5.1 (A)
PYRO2EN: J1.B20 (Pin_20), JP2.1 (A), JP6.1 (A)
PYRO3EN: J1.B22 (Pin_22), JP3.1 (A), JP7.1 (A)
PYRO4EN: J1.B24 (Pin_24), JP4.1 (A), JP8.1 (A)
PYRO_EX+: C10.1, C16.1, D9.1 (K), D13.1 (K), D20.1 (K), D23.1 (K), J1.A23 (Pin_23), J1.A24 (Pin_24), R6.2, R10.1
V_ALL+: C2.2, C5.2, C7.1, C11.1, C12.2, D15.1 (K), D16.1 (K), U1.3 (INPUT), U2.20 (VS), U2.21 (VS), U2.22 (VS), U2.23 (VS), U3.20 (VS), U3.21 (VS), U3.22 (VS), U3.23 (VS), U4.3 (INPUT)

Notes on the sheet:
Power Multiplexer
Battery 1: for 3v3 and 5v lines. Reference point.
Voltage Regulators Overcurrent/ Overvoltage Protection
Connect to LiPo Battery
